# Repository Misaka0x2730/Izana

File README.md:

# Izana
Native hardware platform for Miyako-Link project.
Features:
1. Two communication interfaces: 10/100Base-T Ethernet and USB2.0 High-Speed.
2. Two independent target interfaces, one with isolation up to 1kV.

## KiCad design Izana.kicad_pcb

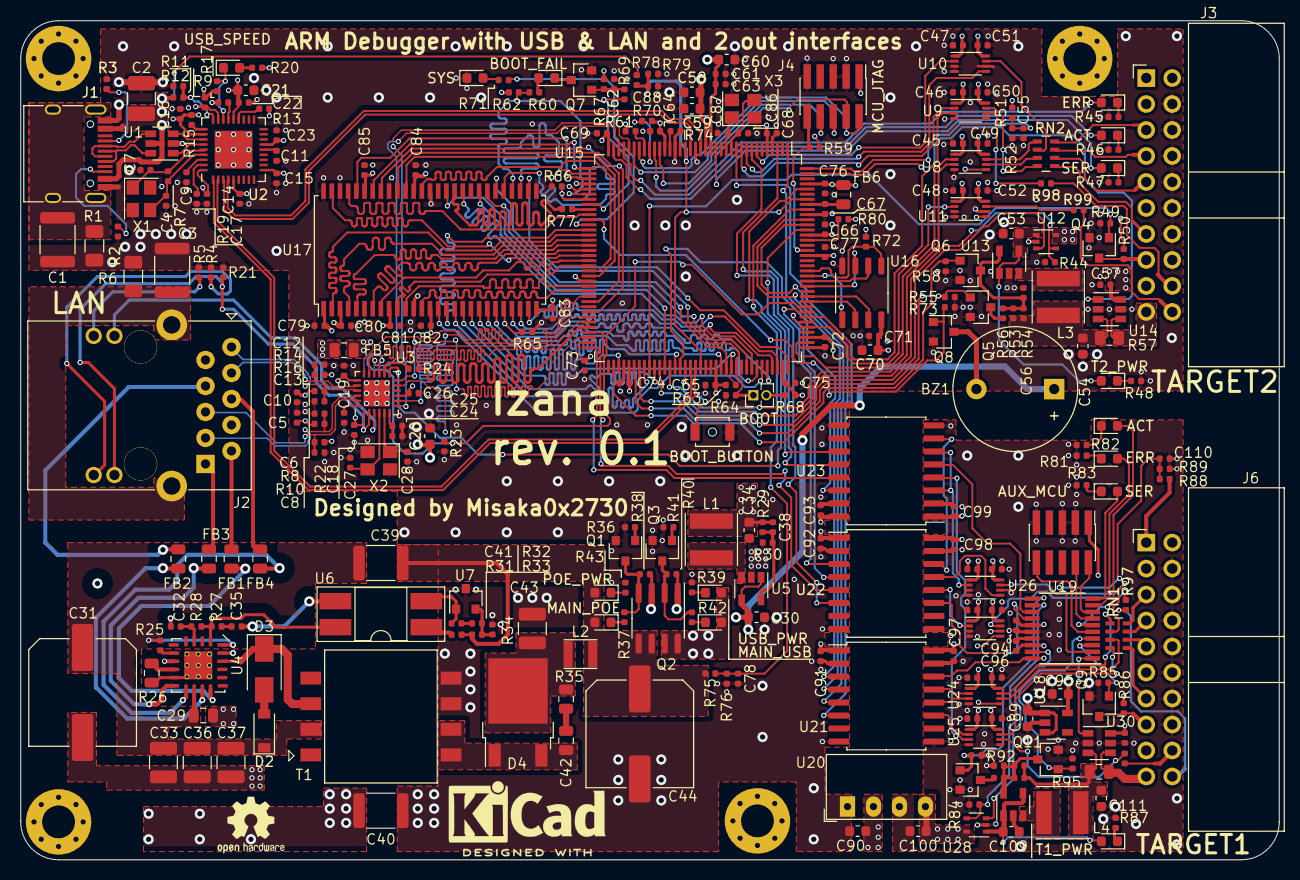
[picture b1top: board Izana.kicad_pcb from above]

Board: 4 copper layers, 123.0 x 82.0 mm, 302 parts (0 on the bottom side), 261 nets.

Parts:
BZ1: Buzzer; Buzzer_12x9.5RM7.6
C1, C3: 4.7nF/2kV; C_1812_4532Metric
C2: 22uF; C_1210_3225Metric_Pad1.42x2.65mm_HandSolder
C4, C7, C86, C87: 18pF; C_0402_1005Metric
C5, C9, C10, C11, C14, C15, C16, C17, C18, C19, C22, C23, C26, C32, C45, C46, C47, C48, C49, C50, C51, C52, C55, C57, C61, C64, C65, C66, C67, C68, C69, C71, C72, C73, C74, C75, C76, C77, C78, C79, C80, C81, C82, C83, C84, C85, C88, C91, C92, C93, C94, C96, C97, C98, C99, C101, C102, C103, C104, C105, C106, C107, C108, C110, C113: 100n; C_0402_1005Metric
C6, C8, C12, C13: 10pF; C_0402_1005Metric
C20, C21, C30, C53, C59, C89, C95, C109: 4.7uF; C_0603_1608Metric
C24, C62: 1uF; C_0402_1005Metric
C25: 470pF; C_0402_1005Metric
C27, C28: 30pF; C_0402_1005Metric
C29: 100n; C_0805_2012Metric
C31: 22uF; C_Elec_10x10.2
C33, C36, C37: 1uF; C_1210_3225Metric
C34, C54, C58, C60, C70, C90, C100, C111: 10uF; C_0603_1608Metric
C35: 15n; C_0402_1005Metric
C38, C56, C112: DNP; C_0402_1005Metric
C39, C40: 1n; C_1812_4532Metric
C41: 3.3n; C_0402_1005Metric
C42: 470p; C_0805_2012Metric
C43: 100uF; C_1210_3225Metric
C44: 1000uF; C_Elec_10x10.2
C63: 10n; C_0402_1005Metric
D1: USB_SPEED; LED_0603_1608Metric
D2: MBR0530; D_SOD-123
D3: SMAJ30A; D_SMA
D4: SSBRD81045T4G; TO-252-2
D5: MAIN_POE; LED_0603_1608Metric
D6: USB_PWR; LED_0603_1608Metric
D7: MAIN_USB; LED_0603_1608Metric
D8: POE_PWR; LED_0603_1608Metric
D9, D15: ERR; LED_0603_1608Metric
D10, D16: ACT; LED_0603_1608Metric
D11, D17: SER; LED_0603_1608Metric
D12: T2_PWR; LED_0603_1608Metric
D13: BOOT_FAIL; LED_0603_1608Metric
D14: SYS; LED_0603_1608Metric
D18: T1_PWR; LED_0603_1608Metric
FB1, FB2, FB3, FB4: BLM21PG331SN1; L_0805_2012Metric
FB5, FB6: BLM21PG121SN1D; L_0805_2012Metric
J1: USB; USB_C_Receptacle_HRO_TYPE-C-31-M-12
J2: LAN; RJ45_Abracon_ARJM11D7-114-AB-EW2
J3: TARGET2; IDC-Header_2x10_P2.54mm_Horizontal
J4: MCU_JTAG; PinHeader_2x05_P1.27mm_Vertical_SMD
J5: AUX_MCU; PinHeader_2x05_P1.27mm_Vertical_SMD
J6: TARGET1; IDC-Header_2x10_P2.54mm_Horizontal
JP1: BOOT; PinHeader_1x02_P1.27mm_Vertical
L1, L3, L4: 2.2uH; L_Taiyo-Yuden_NR-50xx
L2: 1uH; L_Coilcraft_PFL2512
LOGO1: OSHW-Logo2_7.3x6mm_SilkScreen
LOGO2: KiCad-Logo2_6mm_SilkScreen
M1, M2, M3, M4: MountingHole_3.2mm_M3_Pad_Via
Q1, Q3, Q4, Q5, Q6, Q7, Q8, Q9, Q10, Q11: IRLML2502; SOT-23
Q2: IRF7314; SOIC-8_3.9x4.9mm_P1.27mm
R1, R6: 1M; R_1206_3216Metric
R2, R3: 5.1k; R_0402_1005Metric
R4, R5: 270; R_0402_1005Metric
R7: 1M; R_0402_1005Metric
R8, R10, R14, R16: 49.9 1%; R_0402_1005Metric
R9, R11, R12, R13, R15, R17, R18, R30, R36, R38, R40, R41, R44, R51, R52, R54, R55, R58, R59, R61, R62, R63, R64, R65, R66, R67, R70, R72, R73, R75, R76, R78, R79, R80, R84, R88, R89, R91, R92, R95: 100k; R_0402_1005Metric
R19: 12.0k 1%; R_0402_1005Metric
R20, R37, R39, R42, R43, R45, R46, R47, R48, R60, R71, R81, R82, R83, R87: 1.5k; R_0402_1005Metric
R21, R23, R49, R50, R85, R86: 10k; R_0402_1005Metric
R22, R74: 12.1k 1%; R_0402_1005Metric
R24, R96, R97, R98, R99: 33; R_0402_1005Metric
R25: 24.3k; R_0402_1005Metric
R26: 140; R_0805_2012Metric
R27, R32, R77: 0; R_0402_1005Metric
R28, R31, R68: 2.2k; R_0402_1005Metric
R29: 453k; R_0402_1005Metric
R33: 30k 1%; R_0402_1005Metric
R34: 10k 1%; R_0402_1005Metric
R35: 10; R_0805_2012Metric
R53, R90: 200k; R_0402_1005Metric
R56, R93: 82k; R_0402_1005Metric
R57, R94: 0.33 1%; R_0805_2012Metric
R69: 1k; R_0402_1005Metric
RN1, RN2: 33; R_Array_Concave_4x0603
SW1: BOOT_BUTTON; SW_SPST_B3U-1000P-B
T1: Transformer_Coilcraft_FA-2672; Transformer_Coilcraft_FA2672
U1: USBLC6-2SC6; SOT-23-6
U2: USB2512; QFN-36-1EP_6x6mm_P0.5mm_EP3.7x3.7mm
U3: LAN8742A; QFN-24-1EP_4x4mm_P0.5mm_EP2.6x2.6mm
U4: Si3402-B; SiliconLabs_QFN-20-6+6+4+4_1EP_5x5mm_P0.8mm_EP2.75x2.75mm_T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
U5, U13, U29: TLV62568DBV; SOT-23-5
U6: VO615A-3X007T; DIP-4_W8.89mm_SMDSocket_LongPads
U7: TL431DBZ; SOT-23
U8, U9, U10, U11, U24, U25, U26, U27: 74LVC2T45DC; VSSOP-8_2.3x2mm_P0.5mm
U12, U28: FPF2006; SOT-353_SC-70-5
U14, U30: INA181; SOT-23-6
U15: LPC4330FBD144; LQFP-144_20x20mm_P0.5mm
U16: MX25R3235FM1xx0; SOP-8_3.9x4.9mm_P1.27mm
U17: IS42S16400J-xC; TSOP-II-54_22.2x10.16mm_P0.8mm
U18: LP5907MFX-3.3; SOT-23-5
U19: LPC822M101JDH20; TSSOP-20_4.4x6.5mm_P0.65mm
U20: CRE1S0505SC; Converter_DCDC_muRata_CRE1xxxxxxSC_THT
U21, U23: ISO7341C; SOIC-16W_7.5x10.3mm_P1.27mm
U22: ISO7340C; SOIC-16W_7.5x10.3mm_P1.27mm
X1: 24MHz; Crystal_SMD_3225-4Pin_3.2x2.5mm
X2: 25MHz; Crystal_SMD_3225-4Pin_3.2x2.5mm
X3: 12MHz; Crystal_SMD_3225-4Pin_3.2x2.5mm

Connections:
+3.3VP: C94.2, C95.2, C96.1, C113.2, J5.1, U18.5 (OUT), U19.15 (VDD), U19.18 (VREFP), U30.6 (V+)
+3V3: C14.1, C15.1, C16.1, C17.1, C20.1, C21.2, C22.2, C23.2, C26.1, C34.2, C38.2, C45.1, C46.1, C47.1, C48.1, C57.2, C58.2, C59.2, C60.2, C61.2, C63.2, C64.2, C65.2, C66.2, C68.2, C69.2, C70.2, C71.2, C72.2, C73.2, C74.2, C75.2, C76.2, C77.2, C79.2, C80.2, C81.2, C82.2, C83.2, C84.2, C85.2, C91.2, C92.2, C93.2, FB5.2, FB6.2, J4.1, L1.2, R9.1, R13.1, R15.1, R17.1, R20.1, R29.1, R59.1, R61.1, R62.1, R63.1, R67.2, R68.1, R70.1, R72.1, R80.1, U2.5 (VDDA33), U2.10 (VDDA33), U2.15 (VDD33CR), U2.23 (VDD33), U2.29 (VDDA33), U2.36 (VDD33PLL), U3.9 (VDDIO), U8.1 (VCCA), U8.5 (DIR), U9.1 (VCCA), U10.1 (VCCA), U11.1 (VCCA), U11.5 (DIR), U14.6 (V+), U15.5 (VDDIO), U15.16 (USB0_VDDA_3V3_DRIVER), U15.17 (USB0_VDDA3V3), U15.25 (VDDREG), U15.36 (VDDIO), U15.41 (VDDIO), U15.59 (VDDREG), U15.71 (VDDIO), U15.77 (VDDIO), U15.94 (VDDREG), U15.107 (VDDIO), U15.111 (VDDIO), U15.127 (VBAT), U15.131 (VDDREG), U15.141 (VDDIO), U16.8 (VCC), U17.1 (VDD), U17.3 (VDDQ), U17.9 (VDDQ), U17.14 (VDD), U17.27 (VDD), U17.43 (VDDQ), U17.49 (VDDQ), U21.1 (VCC1), U22.1 (VCC1), U23.16 (VCC2)
+5V: BZ1.1 (-), C30.2, C90.1, Q2.1 (S1), Q2.3 (S2), R38.1, R40.1, U5.1 (EN), U5.4 (VIN), U12.5 (IN), U20.2 (+VIN)
+5VP: C89.2, C97.2, C98.2, C99.2, C100.1, C101.1, C102.1, C103.1, C104.1, U18.1 (IN), U18.3 (EN), U20.4 (+VOUT), U21.16 (VCC2), U22.16 (VCC2), U23.1 (VCC1), U24.1 (VCCA), U24.5 (DIR), U25.1 (VCCA), U26.1 (VCCA), U27.1 (VCCA), U27.5 (DIR), U28.5 (IN)
/Izana_Input_Interface/ETH_CT: C5.2, C10.2, C18.2, C19.2, FB5.1, J2.4 (RCT), J2.9 (TCT), R8.1, R10.1, R14.1, R16.1, U3.1 (VDD2A), U3.19 (VDD1A)
/Izana_Input_Interface/ETH_LED1: J2.L1 (LLED+), U3.3 (LED1/nINT/nPME/REGOFF)
/Izana_Input_Interface/ETH_LED2: J2.L3 (RLED+), R21.1, U3.2 (LED2/nINT/nPME/nINTSEL)
/Izana_Input_Interface/ETH_RX_N: C6.2, J2.3 (RD-), R8.2, U3.22 (RXN)
/Izana_Input_Interface/ETH_RX_P: C8.2, J2.5 (RD+), R10.2, U3.23 (RXP)
/Izana_Input_Interface/ETH_TX_N: C12.2, J2.8 (TD-), R14.2, U3.20 (TXN)
/Izana_Input_Interface/ETH_TX_P: C13.2, J2.10 (TD+), R16.2, U3.21 (TXP)
/Izana_Input_Interface/USB_DATA_N: J1.A7 (D-), J1.B7 (D-), U1.4 (IO2)
/Izana_Input_Interface/USB_DATA_P: J1.A6 (D+), J1.B6 (D+), U1.6 (IO1)
/Izana_Input_Interface/USB_DATA_PROTECT_N: U1.3 (IO2), U2.30 (USBUP_DM)
/Izana_Input_Interface/USB_DATA_PROTECT_P: U1.1 (IO1), U2.31 (USBUP_DP)
/Izana_MCU/BOOT_BUTTON: SW1.2, U15.88 (P2_4)
/Izana_MCU/BUZZER: Q8.1 (G), R73.1, U15.47 (P1_4)
/Izana_MCU/FLASH_CLK: U15.118 (P3_3), U16.6 (SCLK)
/Izana_MCU/FLASH_IO0: U15.123 (P3_7), U16.5 (SI/SIO0)
/Izana_MCU/FLASH_IO1: U15.122 (P3_6), U16.2 (SO/SIO1)
/Izana_MCU/FLASH_IO2: U15.121 (P3_5), U16.3 (~WP~/SIO2)
/Izana_MCU/FLASH_IO3: U15.119 (P3_4), U16.7 (~RESET~/SIO3)
/Izana_MCU/FLASH_~CS: R72.2, U15.124 (P3_8), U16.1 (~CS)
/Izana_MCU/MCU_BOOT_LED_DISABLE: R69.1, U15.44 (P1_3)
/Izana_MCU/MCU_TCK: J4.4, U15.27 (TCK/SWDCLK)
/Izana_MCU/MCU_TDI: J4.8, U15.26 (TDI)
/Izana_MCU/MCU_TDO: J4.6, U15.31 (TDO/SWO)
/Izana_MCU/MCU_TMS: J4.2, U15.30 (TMS/SWDIO)
/Izana_MCU/MCU_~RESET: J4.10, R59.2, U15.128 (~RESET)
/Izana_MCU/POE_DETECT_ADC: C78.1, R75.2, R76.1, U15.136 (ADC0_7/ADC1_7)
/Izana_MCU/SDRAM_A0\BOOT0: R65.2, U15.102 (P2_9), U17.23 (A0)
/Izana_MCU/SDRAM_A1: U15.104 (P2_10), U17.24 (A1)
/Izana_MCU/SDRAM_A2: U15.105 (P2_11), U17.25 (A2)
/Izana_MCU/SDRAM_A3: U15.106 (P2_12), U17.26 (A3)
/Izana_MCU/SDRAM_A4: U15.108 (P2_13), U17.29 (A4)
/Izana_MCU/SDRAM_A5: U15.38 (P1_0), U17.30 (A5)
/Izana_MCU/SDRAM_A6\BOOT3: R60.2, R62.2, U15.42 (P1_1), U17.31 (A6)
/Izana_MCU/SDRAM_A7\BOOT2: R66.2, U15.43 (P1_2), U17.32 (A7)
/Izana_MCU/SDRAM_A8\BOOT1: JP1.1, R64.2, U15.98 (P2_8), U17.33 (A8)
/Izana_MCU/SDRAM_A9\BOOT4: R63.2, U15.96 (P2_7), U17.34 (A9)
/Izana_MCU/SDRAM_A10: U15.95 (P2_6), U17.22 (A10)
/Izana_MCU/SDRAM_A11: U15.84 (P2_2), U17.35 (A11)
/Izana_MCU/SDRAM_BA0: U15.75 (P2_0), U17.20 (BA0)
/Izana_MCU/SDRAM_BA1: U15.86 (P6_8), U17.21 (BA1)
/Izana_MCU/SDRAM_CKE: U15.101 (P6_11), U17.37 (CKE)
/Izana_MCU/SDRAM_CLK: R77.2, U15.45 (CLK0)
/Izana_MCU/SDRAM_DQ0: U15.50 (P1_7), U17.2 (DQ0)
/Izana_MCU/SDRAM_DQ1: U15.51 (P1_8), U17.4 (DQ1)
/Izana_MCU/SDRAM_DQ2: U15.52 (P1_9), U17.5 (DQ2)
/Izana_MCU/SDRAM_DQ3: U15.53 (P1_10), U17.7 (DQ3)
/Izana_MCU/SDRAM_DQ4: U15.55 (P1_11), U17.8 (DQ4)
/Izana_MCU/SDRAM_DQ5: U15.56 (P1_12), U17.10 (DQ5)
/Izana_MCU/SDRAM_DQ6: U15.60 (P1_13), U17.11 (DQ6)
/Izana_MCU/SDRAM_DQ7: U15.61 (P1_14), U17.13 (DQ7)
/Izana_MCU/SDRAM_DQ8: U15.57 (P5_4), U17.42 (DQ8)
/Izana_MCU/SDRAM_DQ9: U15.58 (P5_5), U17.44 (DQ9)
/Izana_MCU/SDRAM_DQ10: U15.63 (P5_6), U17.45 (DQ10)
/Izana_MCU/SDRAM_DQ11: U15.65 (P5_7), U17.47 (DQ11)
/Izana_MCU/SDRAM_DQ12: U15.37 (P5_0), U17.48 (DQ12)
/Izana_MCU/SDRAM_DQ13: U15.39 (P5_1), U17.50 (DQ13)
/Izana_MCU/SDRAM_DQ14: U15.46 (P5_2), U17.51 (DQ14)
/Izana_MCU/SDRAM_DQ15: U15.54 (P5_3), U17.53 (DQ15)
/Izana_MCU/SDRAM_LDQM: U15.103 (P6_12), U17.15 (LDQM)
/Izana_MCU/SDRAM_UDQM: U15.100 (P6_10), U17.39 (UDQM)
/Izana_MCU/SDRAM_~CAS: U15.80 (P6_4), U17.17 (~CAS)
/Izana_MCU/SDRAM_~CS: U15.97 (P6_9), U17.19 (~CS)
/Izana_MCU/SDRAM_~RAS: U15.82 (P6_5), U17.18 (~RAS)
/Izana_MCU/SDRAM_~WE: U15.49 (P1_6), U17.16 (~WE)
/Izana_MCU/SYS_LED: R71.2, U15.48 (P1_5)
/Izana_MCU/USB_VBUS_DETECT: C88.1, R78.2, R79.1, U15.21 (USB0_VBUS), U15.91 (P2_5), U15.138 (ADC0_4/ADC1_4)
/Izana_Target_1_Iso/TARGET1_BUF_TCK: RN1.7 (R2.2), U24.6 (2B)
/Izana_Target_1_Iso/TARGET1_BUF_TDI: RN1.5 (R4.2), U24.7 (1B)
/Izana_Target_1_Iso/TARGET1_BUF_TDO: RN1.8 (R1.2), U25.7 (1B)
/Izana_Target_1_Iso/TARGET1_BUF_TMS: RN1.6 (R3.2), U26.7 (1B)
/Izana_Target_1_Iso/TARGET1_BUF_UART_RX: R97.1, U27.7 (1B)
/Izana_Target_1_Iso/TARGET1_BUF_UART_TX: R96.1, U25.6 (2B)
/Izana_Target_1_Iso/TARGET1_BUF_~RST: J6.15, Q9.3 (D), R86.2
/Izana_Target_1_Iso/TARGET1_CURR_ADC: U19.1 (PIO0_23), U30.1
/Izana_Target_1_Iso/TARGET1_ISO_AUX_SWCLK: J5.4, U19.7 (PIO0_3)
/Izana_Target_1_Iso/TARGET1_ISO_AUX_SWDIO: J5.2, U19.8 (PIO0_2)
/Izana_Target_1_Iso/TARGET1_ISO_AUX_~RST: J5.10, U19.5 (PIO0_5)
/Izana_Target_1_Iso/TARGET1_ISO_CTRL_CLK: U19.20 (PIO0_14), U21.14 (OUTA)
/Izana_Target_1_Iso/TARGET1_ISO_CTRL_RX: U19.14 (PIO0_8), U22.11 (OUTD)
/Izana_Target_1_Iso/TARGET1_ISO_CTRL_TX: U19.13 (PIO0_9), U23.5 (INC)
/Izana_Target_1_Iso/TARGET1_ISO_TCK: U21.12 (OUTC), U24.3 (2A)
/Izana_Target_1_Iso/TARGET1_ISO_TDI: U21.13 (OUTB), U24.2 (1A)
/Izana_Target_1_Iso/TARGET1_ISO_TDO: U21.11 (IND), U25.2 (1A)
/Izana_Target_1_Iso/TARGET1_ISO_TMS: U23.3 (INA), U23.6 (OUTD), U26.2 (1A)
/Izana_Target_1_Iso/TARGET1_ISO_TMS_DIR_BUF: U22.13 (OUTB), U26.5 (DIR)
/Izana_Target_1_Iso/TARGET1_ISO_TMS_DIR_OUT: U22.14 (OUTA), U23.7 (EN1)
/Izana_Target_1_Iso/TARGET1_ISO_UART_RX: U22.12 (OUTC), U27.2 (1A)
/Izana_Target_1_Iso/TARGET1_ISO_UART_TX: U23.4 (INB), U25.3 (2A)
/Izana_Target_1_Iso/TARGET1_ISO_VREF: C105.2, C106.2, C107.2, C108.2, J6.1, R86.1, R88.1, U24.8 (VCCB), U25.8 (VCCB), U26.8 (VCCB), U27.8 (VCCB)
/Izana_Target_1_Iso/TARGET1_ISO_~RST: Q9.1 (G), R85.1, U19.3 (PIO0_13)
/Izana_Target_1_Iso/TARGET1_LED_ACT: D16.2 (A), U19.6 (PIO0_4)
/Izana_Target_1_Iso/TARGET1_LED_ERR: D15.2 (A), U19.9 (PIO0_11)
/Izana_Target_1_Iso/TARGET1_LED_SER: D17.2 (A), U19.10 (PIO0_10)
/Izana_Target_1_Iso/TARGET1_PWR: J6.19, R94.2, U30.4 (-)
/Izana_Target_1_Iso/TARGET1_PWR_1: Q10.1 (G), R92.1, U19.11 (PIO0_15)
/Izana_Target_1_Iso/TARGET1_PWR_2: Q11.1 (G), R95.1, U19.4 (PIO0_12)
/Izana_Target_1_Iso/TARGET1_PWR_ENABLE: R84.1, U19.12 (PIO0_1), U28.4 (ON)
/Izana_Target_1_Iso/TARGET1_PWR_~OC: U19.19 (PIO0_0), U28.3 (FLAGB)
/Izana_Target_1_Iso/TARGET1_VREF_ADC: C110.2, R88.2, R89.1, U19.2 (PIO0_17)
/Izana_Target_2/TARGET2_BUF_TCK: RN2.7 (R2.2), U8.6 (2B)
/Izana_Target_2/TARGET2_BUF_TDI: RN2.5 (R4.2), U8.7 (1B)
/Izana_Target_2/TARGET2_BUF_TDO: RN2.8 (R1.2), U9.7 (1B)
/Izana_Target_2/TARGET2_BUF_TMS: RN2.6 (R3.2), U10.7 (1B)
/Izana_Target_2/TARGET2_BUF_UART_RX: R99.2, U11.7 (1B)
/Izana_Target_2/TARGET2_BUF_UART_TX: R98.2, U9.6 (2B)
/Izana_Target_2/TARGET2_BUF_VREF: C49.2, C50.2, C51.2, C52.2, J3.1, R50.1, R51.1, U8.8 (VCCB), U9.8 (VCCB), U10.8 (VCCB), U11.8 (VCCB)
/Izana_Target_2/TARGET2_BUF_~RST: J3.15, Q4.3 (D), R50.2
/Izana_Target_2/TARGET2_PWR: J3.19, R57.2, U14.4 (-)
/POE_5V: C39.1, C44.1, D5.2 (A), D8.2 (A), L2.2, Q2.5 (D2), Q2.6 (D2), R31.1, R33.1, R75.1
/POE_CT1: FB1.2, U4.14 (CT1)
/POE_CT2: FB2.2, U4.13 (CT2)
/POE_EN: Q1.1 (G), R36.1
/POE_SP1: FB4.2, U4.11 (SP1)
/POE_SP2: FB3.2, U4.10 (SP2)
/RMII_CRS_DV: U3.11 (CRS_DV/MODE2), U15.64 (P1_16)
/RMII_MDC: U3.13 (MDC), U15.140 (P7_7)
/RMII_MDIO: U3.12 (MDIO), U15.66 (P1_17)
/RMII_REF_CLK: R24.1, U15.68 (P1_19)
/RMII_RXD0: U3.8 (RXD0/MODE0), U15.62 (P1_15)
/RMII_RXD1: U3.7 (RXD1/MODE1), U15.32 (P0_0)
/RMII_TXD0: U3.17 (TXD0), U15.67 (P1_18)
/RMII_TXD1: U3.18 (TXD1), U15.70 (P1_20)
/RMII_TXEN: U3.16 (TXEN), U15.34 (P0_1)
/RMII_~RST: R23.1, U3.15 (RST), U15.117 (P7_3)
/TARGET1_CTRL_CLK: U15.1 (P4_0), U21.3 (INA)
/TARGET1_CTRL_TX: U15.8 (P4_2), U23.12 (OUTC)
/TARGET1_CTRL_TX_1: U15.3 (P4_1), U22.6 (IND)
/TARGET1_TCK: U15.133 (P7_5), U21.5 (INC)
/TARGET1_TDI: U15.134 (P7_6), U21.4 (INB)
/TARGET1_TDO: U15.11 (P4_6), U21.6 (OUTD)
/TARGET1_TMS_DIR_BUF: U15.114 (P3_1), U22.4 (INB)
/TARGET1_TMS_DIR_OUT: U15.116 (P3_2), U22.3 (INA)
/TARGET1_TMS_IN: U15.87 (P2_3), U23.14 (OUTA)
/TARGET1_TMS_OUT: U15.132 (P7_4), U23.11 (IND)
/TARGET1_UART_TX: U15.69 (P9_5), U22.5 (INC)
/TARGET1_UART_TX_1: U15.72 (P9_6), U23.13 (OUTB)
/TARGET2_CURR_ADC: U14.1, U15.143 (ADC0_2/ADC1_2)
/TARGET2_LED_ACT: D10.2 (A), U15.35 (P4_10)
/TARGET2_LED_ERR: D9.2 (A), U15.33 (P4_9)
/TARGET2_LED_SER: D11.2 (A), U15.15 (P4_8)
/TARGET2_PWR_1: Q5.1 (G), R55.1, U15.78 (P6_2)
/TARGET2_PWR_2: Q6.1 (G), R58.1, U15.74 (P6_1)
/TARGET2_PWR_ENABLE: R44.1, U12.4 (ON), U15.83 (P6_6)
/TARGET2_PWR_~OC: U12.3 (FLAGB), U15.79 (P6_3)
/TARGET2_TCK: U8.3 (2A), U15.85 (P6_7)
/TARGET2_TDI: U8.2 (1A), U15.110 (P7_0)
/TARGET2_TDO: U9.2 (1A), U15.10 (P4_5)
/TARGET2_TMS: U10.2 (1A), U15.7 (P4_3)
/TARGET2_TMS_DIR: U10.5 (DIR), U15.9 (P4_4)
/TARGET2_UART_TX: U9.3 (2A), U15.115 (P7_2)
/TARGET2_UART_TX_1: U11.2 (1A), U15.113 (P7_1)
/TARGET2_VREF_ADC: C55.2, R51.2, R52.1, U15.144 (ADC0_5/ADC1_5)
/TARGET2_~RST: Q4.1 (G), R49.1, U15.81 (P2_1)
/USB_5V: C2.2, D6.2 (A), D7.2 (A), J1.A4 (VBUS), J1.A9 (VBUS), J1.B4 (VBUS), J1.B9 (VBUS), Q2.7 (D1), Q2.8 (D1), R11.1, R78.1, U1.5 (VBUS)
/USB_AUX_N: U2.1 (USBDN1_DM), U15.90 (USB1_DM)
/USB_AUX_P: U2.2 (USBDN1_DP), U15.89 (USB1_DP)
/USB_EN: Q3.1 (G), R41.1
/USB_MAIN_N: U2.3 (USBDN2_DM), U15.20 (USB0_DM)
/USB_MAIN_P: U2.4 (USBDN2_DP), U15.18 (USB0_DP)
/USB_~RST: R9.2, U2.26 (RESET_N)
GND: C1.2, C2.1, C3.2, C4.1, C5.1, C6.1, C7.1, C8.1, C9.1, C10.1, C11.1, C12.1, C13.1, C14.2, C15.2, C16.2, C17.2, C18.1, C19.1, C20.2, C21.1, C22.1, C23.1, C24.2, C25.2, C26.2, C27.1, C28.1, C30.1, C34.1, C40.1, C43.1, C44.2, C45.2, C46.2, C47.2, C48.2, C49.1, C50.1, C51.1, C52.1, C53.1, C54.1, C55.1, C57.1, C58.1, C59.1, C60.1, C61.1, C62.1, C63.1, C64.1, C65.1, C66.1, C67.1, C68.1, C69.1, C70.1, C71.1, C72.1, C73.1, C74.1, C75.1, C76.1, C77.1, C78.2, C79.1, C80.1, C81.1, C82.1, C83.1, C84.1, C85.1, C86.1, C87.1, C88.2, C90.2, C91.1, C92.1, C93.1, D14.1 (K), J1.A1 (GND), J1.A12 (GND), J1.B1 (GND), J1.B12 (GND), J3.4, J3.6, J3.8, J3.10, J3.12, J3.14, J3.16, J4.3, J4.5, J4.9, Q1.2 (S), Q3.2 (S), Q4.2 (S), Q5.2 (S), Q6.2 (S), Q7.2 (S), Q8.2 (S), R1.2, R2.2, R3.2, R4.2, R5.2, R6.2, R12.2, R18.1, R19.2, R21.2, R22.2, R23.2, R30.2, R34.2, R36.2, R39.1, R41.2, R43.1, R44.2, R45.2, R46.2, R47.2, R48.2, R49.2, R52.2, R54.2, R55.2, R58.2, R64.1, R65.1, R66.1, R73.2, R74.2, R76.2, R79.2, SW1.1, T1.7 (S1), T1.8 (S3), U1.2 (GND), U2.37 (VSS), U3.25 (VSS), U5.2 (GND), U7.3 (A), U8.4 (GND), U9.4 (GND), U9.5 (DIR), U10.3 (2A), U10.4 (GND), U10.6 (2B), U11.3 (2A), U11.4 (GND), U11.6 (2B), U12.2 (GND), U13.2 (GND), U14.2 (GND), U14.5 (REF), U15.4 (VSSIO), U15.19 (USB0_VSSA_TERM), U15.23 (USB0_VSSA_REF), U15.40 (VSSIO), U15.76 (VSSIO), U15.109 (VSSIO), U15.135 (VSSA), U16.4 (GND), U17.6 (GNDQ), U17.12 (GNDQ), U17.28 (GND), U17.41 (GND), U17.46 (GNDQ), U17.52 (GNDQ), U17.54 (GND), U20.1 (-VIN), U21.2 (GND1), U21.8 (GND1), U22.2 (GND1), U22.8 (GND1), U23.9 (GND2), U23.15 (GND2), X1.2, X1.4, X2.2, X2.4, X3.2, X3.4
GNDD: C89.1, C94.1, C95.1, C96.2, C97.1, C98.1, C99.1, C100.2, C101.2, C102.2, C103.2, C104.2, C105.1, C106.1, C107.1, C108.1, C109.1, C110.1, C111.1, C113.1, J5.3, J5.5, J5.9, J6.4, J6.6, J6.8, J6.10, J6.12, J6.14, J6.16, Q9.2 (S), Q10.2 (S), Q11.2 (S), R81.2, R82.2, R83.2, R84.2, R85.2, R87.2, R89.2, R91.2, R92.2, R95.2, U18.2 (GND), U19.16 (VSS), U19.17 (VREFN), U20.3 (-VOUT), U21.9 (GND2), U21.15 (GND2), U22.9 (GND2), U22.15 (GND2), U23.2 (GND1), U23.8 (GND1), U24.4 (GND), U25.4 (GND), U25.5 (DIR), U26.3 (2A), U26.4 (GND), U26.6 (2B), U27.3 (2A), U27.4 (GND), U27.6 (2B), U28.2 (GND), U29.2 (GND), U30.2 (GND), U30.5 (REF)
GNDPWR: C29.1, C40.2, R26.2, U4.9 (VNEG), U4.21 (VNEG)
unnamed: BZ1.2 (+), Q8.3 (D)
unnamed: C1.1, J1.S1 (SHIELD), R1.1
unnamed: C3.1, J2.11 (SHIELD), R6.1
unnamed: C4.2, R7.1, U2.33 (XTALIN/CLKIN), X1.3
unnamed: C7.2, R7.2, U2.32 (XTALOUT), X1.1
unnamed: C9.2, U2.34 (VDD18PLL)
unnamed: C11.2, U2.14 (VDD18)
unnamed: C24.1, C25.1, U3.6 (VDDCR)
unnamed: C27.2, U3.4 (XTAL2), X2.3
unnamed: C28.2, U3.5 (XTAL1/CLKIN), X2.1
unnamed: C29.2, C31.1, C33.2, C36.2, C37.2, C39.2, D2.1 (K), R25.2, T1.2 (PR2), U4.12 (VPOSF), U4.20 (FB)
unnamed: C31.2, C32.1, C33.1, C35.1, C36.1, C37.1, U4.7 (HSO), U4.19 (VSS2), U6.3
unnamed: C32.2, R28.1, U4.3 (VDD)
unnamed: C35.2, R27.2
unnamed: C38.1, R29.2, R30.1, U5.5 (FB)
unnamed: C41.1, U6.2, U7.1 (K)
unnamed: C41.2, R32.1
unnamed: C42.1, R35.1
unnamed: C42.2, D4.1 (A), D4.3 (A), T1.5 (S2), T1.6 (S4)
unnamed: C43.2, D4.2 (K), L2.1, R35.2
unnamed: C53.2, D12.2 (A), U12.1 (OUT), U13.1 (EN), U13.4 (VIN)
unnamed: C54.2, C56.2, L3.2, R53.1, R57.1, U14.3 (+)
unnamed: C56.1, Q6.3 (D), R53.2, R54.1, R56.1, U13.5 (FB)
unnamed: C62.2, Q7.1 (G), R67.1, R69.2
unnamed: C67.2, FB6.1, U15.137 (VDDA)
unnamed: C86.2, U15.12 (XTAL1), X3.3
unnamed: C87.2, U15.13 (XTAL2), X3.1
unnamed: C109.2, D18.2 (A), U28.1 (OUT), U29.1 (EN), U29.4 (VIN)
unnamed: C111.2, C112.2, L4.2, R90.1, R94.1, U30.3 (+)
unnamed: C112.1, Q11.3 (D), R90.2, R91.1, R93.1, U29.5 (FB)
unnamed: D1.1 (K), R17.2, U2.25 (HS_IND/CFG_SEL1)
unnamed: D1.2 (A), R20.2
unnamed: D2.2 (A), D3.2 (A)
unnamed: D3.1 (K), T1.3 (PR1), U4.18 (SWO)
unnamed: D5.1 (K), R37.2
unnamed: D6.1 (K), R39.2
unnamed: D7.1 (K), R42.2
unnamed: D8.1 (K), R43.2
unnamed: D9.1 (K), R45.1
unnamed: D10.1 (K), R46.1
unnamed: D11.1 (K), R47.1
unnamed: D12.1 (K), R48.1
unnamed: D13.1 (K), Q7.3 (D)
unnamed: D13.2 (A), R60.1
unnamed: D14.2 (A), R71.1
unnamed: D15.1 (K), R81.1
unnamed: D16.1 (K), R82.1
unnamed: D17.1 (K), R83.1
unnamed: D18.1 (K), R87.1
unnamed: FB1.1, J2.2 (VC1-)
unnamed: FB2.1, J2.7 (VC1+)
unnamed: FB3.1, J2.1 (VC2-)
unnamed: FB4.1, J2.6 (VC2+)
unnamed: J1.A5 (CC1), R3.1
unnamed: J1.B5 (CC2), R2.1
unnamed: J2.L2 (LLED-), R5.1
unnamed: J2.L4 (RLED-), R4.1
unnamed: J3.5, RN2.4 (R4.1)
unnamed: J3.7, RN2.3 (R3.1)
unnamed: J3.9, RN2.2 (R2.1)
unnamed: J3.13, RN2.1 (R1.1)
unnamed: J3.18, R98.1
unnamed: J3.20, R99.1
unnamed: J6.5, RN1.4 (R4.1)
unnamed: J6.7, RN1.3 (R3.1)
unnamed: J6.9, RN1.2 (R2.1)
unnamed: J6.13, RN1.1 (R1.1)
unnamed: J6.18, R96.2
unnamed: J6.20, R97.2
unnamed: JP1.2, R68.2
unnamed: L1.1, U5.3 (SW)
unnamed: L3.1, U13.3 (SW)
unnamed: L4.1, U29.3 (SW)
unnamed: Q1.3 (D), Q2.4 (G2), R37.1, R38.2
unnamed: Q2.2 (G1), Q3.3 (D), R40.2, R42.1
unnamed: Q5.3 (D), R56.2
unnamed: Q10.3 (D), R93.2
unnamed: R11.2, R12.1, U2.27 (VBUS_DET)
unnamed: R13.2, U2.22 (SDA/SMBDATA/NON_REM1)
unnamed: R15.2, U2.28 (SUSP_IND/LOCAL_PWR/NON_REM0)
unnamed: R18.2, U2.24 (SCL/SMBCLK/CFG_SEL0)
unnamed: R19.1, U2.35 (RBIAS)
unnamed: R22.1, U3.24 (RBIAS)
unnamed: R24.2, U3.14 (INT/REFCLKO)
unnamed: R25.1, U4.6 (RDET)
unnamed: R26.1, U4.8 (RCL)
unnamed: R27.1, R28.2, U4.1 (EROUT), U6.4
unnamed: R31.2, U6.1
unnamed: R32.2, R33.2, R34.1, U7.2 (REF)
unnamed: R61.2, U15.29 (~TRST)
unnamed: R70.2, U15.28 (DBGEN)
unnamed: R74.1, U15.24 (USB0_RREF)
unnamed: R77.1, U17.38 (CLK)
unnamed: R80.2, U15.130 (WAKEUP0)

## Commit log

2020-03-28 Completed ETH, SDRAM, PoE routing
2020-04-14 Schematic and pcb has been completed
2020-07-26 Added BOM
